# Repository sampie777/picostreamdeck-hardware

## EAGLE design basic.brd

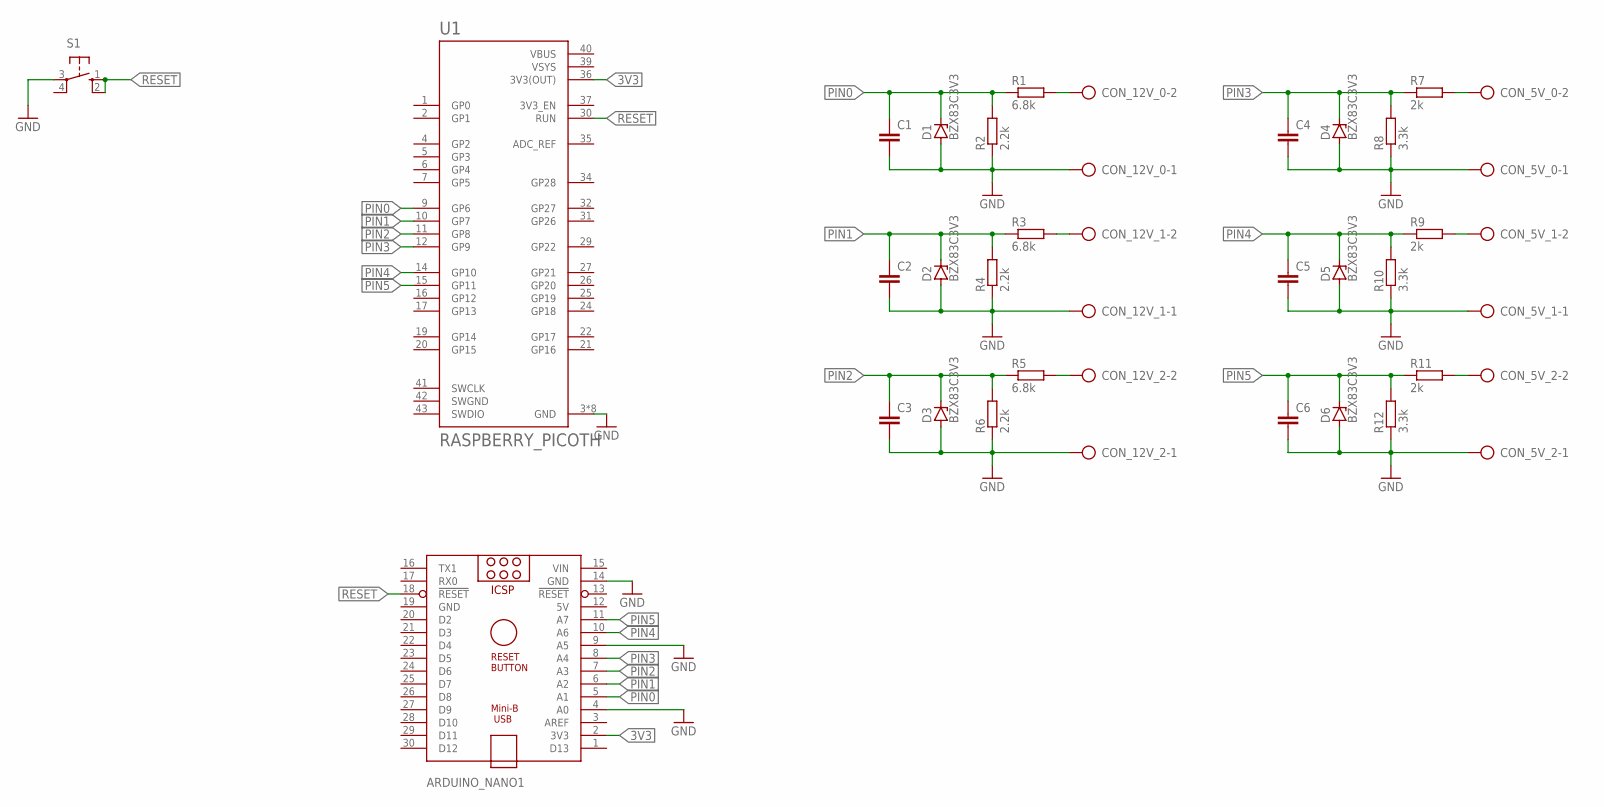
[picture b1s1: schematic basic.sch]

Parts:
ARDUINO_NANO1: ARDUINO_NANO
C1, C2, C3, C4, C5, C6: C-EU025-050X050; C025-050X050
CON_5V_0, CON_5V_1, CON_5V_2, CON_12V_0, CON_12V_1, CON_12V_2: AK300/2
D1, D2, D3, D4, D5, D6: BZX83C3V3; DO41Z7.6
R1, R3, R5: 6.8k; 0207/7
R2, R4, R6: 2.2k; 0207/7
R7, R9, R11: 2k; 0207/7
R8, R10, R12: 3.3k; 0207/7
S1: 10-XX; B3F-10XX
U1: RASPBERRY_PICOTH; PICO-PKG-TH

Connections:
3V3: ARDUINO_NANO1.2 (3V3), U1.36 (3V3(OUT))
5V: ARDUINO_NANO1.12 (5V)
GND: ARDUINO_NANO1.4 (A0), ARDUINO_NANO1.9 (A5), ARDUINO_NANO1.14 (GND), ARDUINO_NANO1.19 (GND), C1.2, C2.2, C3.2, C4.2, C5.2, C6.2, CON_5V_0.1, CON_5V_1.1, CON_5V_2.1, CON_12V_0.1, CON_12V_1.1, CON_12V_2.1, D1.A, D2.A, D3.A, D4.A, D5.A, D6.A, R2.1, R4.1, R6.1, R8.1, R10.1, R12.1, S1.3, U1.3 (GND), U1.8 (GND), U1.13 (GND), U1.18 (GND), U1.23 (GND), U1.28 (GND), U1.33 (GND), U1.38 (GND)
unnamed: CON_12V_0.2, R1.2
unnamed: CON_12V_1.2, R3.2
unnamed: CON_12V_2.2, R5.2
unnamed: CON_5V_0.2, R7.2
unnamed: CON_5V_1.2, R9.2
unnamed: CON_5V_2.2, R11.2
PIN0: ARDUINO_NANO1.5 (A1), C1.1, D1.C, R1.1, R2.2, U1.9 (GP6)
PIN1: ARDUINO_NANO1.6 (A2), C2.1, D2.C, R3.1, R4.2, U1.10 (GP7)
PIN2: ARDUINO_NANO1.7 (A3), C3.1, D3.C, R5.1, R6.2, U1.11 (GP8)
PIN3: ARDUINO_NANO1.8 (A4), C4.1, D4.C, R7.1, R8.2, U1.12 (GP9)
PIN4: ARDUINO_NANO1.10 (A6), C5.1, D5.C, R9.1, R10.2, U1.14 (GP10)
PIN5: ARDUINO_NANO1.11 (A7), C6.1, D6.C, R11.1, R12.2, U1.15 (GP11)
RESET: ARDUINO_NANO1.18 (!RESET), S1.1 (S), S1.2 (S1), U1.30 (RUN)
SWGND: U1.42 (SWGND)
VBUS: U1.40 (VBUS)
VIN: ARDUINO_NANO1.15 (VIN)
VSYS: U1.39 (VSYS)

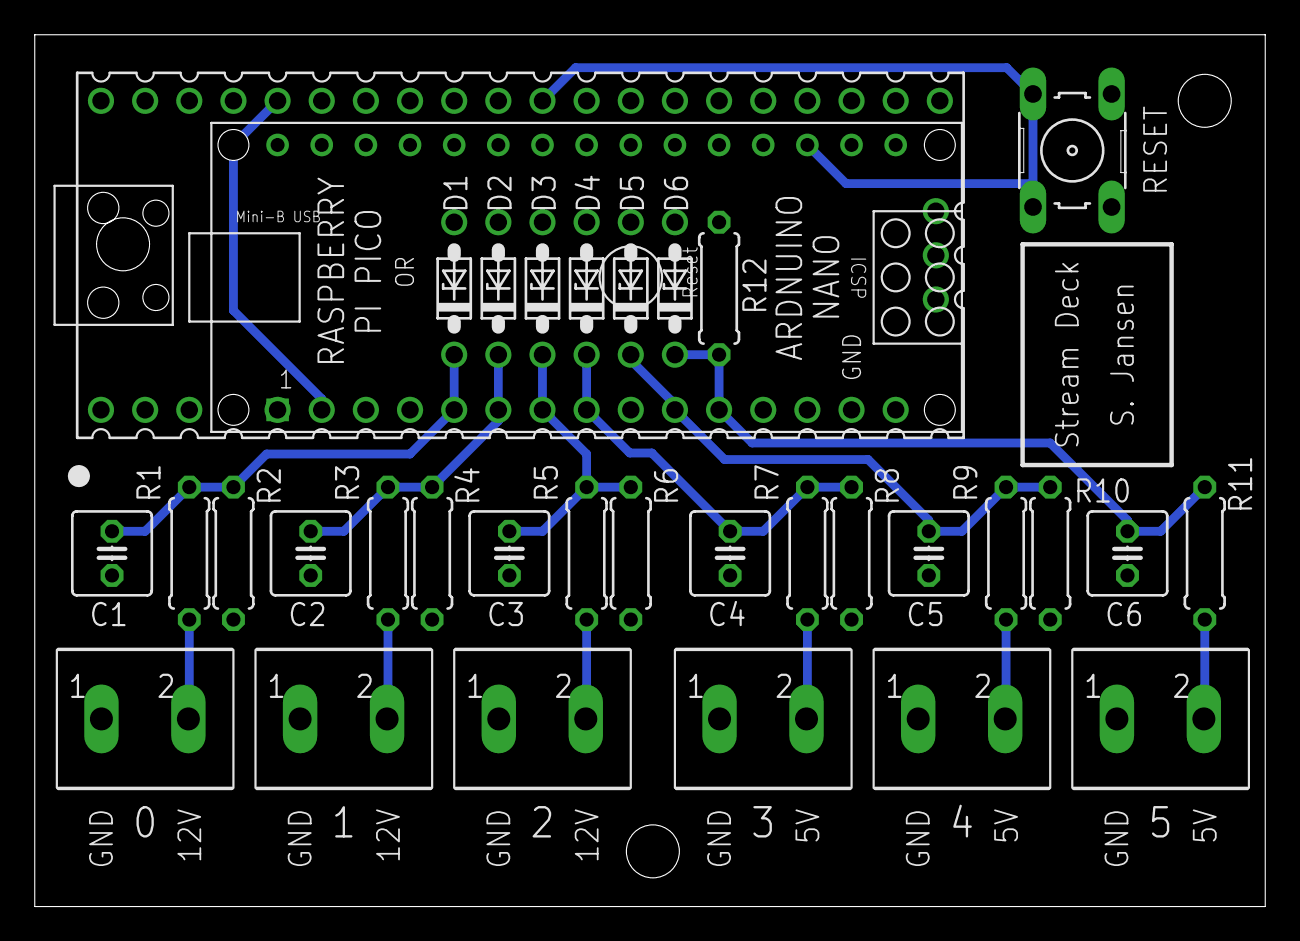
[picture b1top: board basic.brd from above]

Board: 2 copper layers, 70.8 x 50.2 mm, 33 parts (0 on the bottom side), 15 nets.

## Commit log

2023-02-22 initial board layout
2023-02-22 Renamed project
2023-02-22 no idea why this file has changed
2023-02-22 Added capacitors to catch voltage spikes
